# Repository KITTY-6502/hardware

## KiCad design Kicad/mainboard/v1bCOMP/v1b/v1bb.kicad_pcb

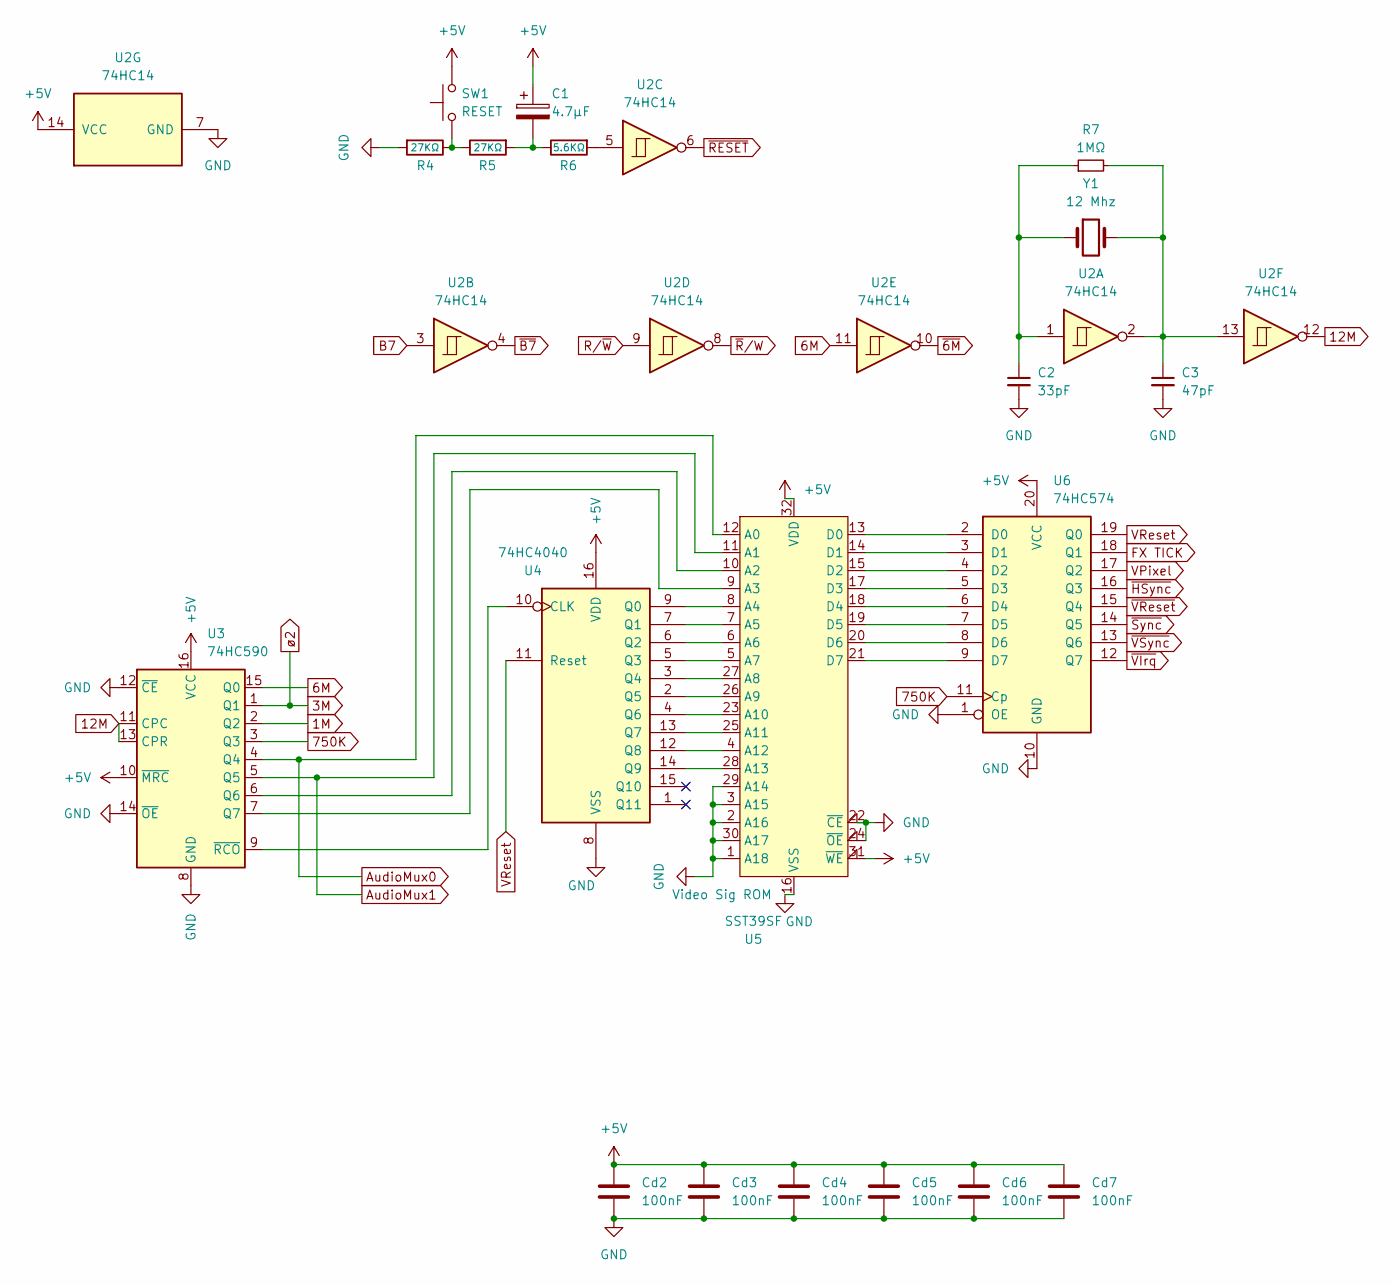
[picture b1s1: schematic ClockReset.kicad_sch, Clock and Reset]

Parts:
C1: 4.7µF; CP_Radial_D4.0mm_P1.50mm
C2: 33pF; C_Disc_D3.0mm_W2.0mm_P2.50mm
C3: 47pF; C_Disc_D3.0mm_W2.0mm_P2.50mm
Cd2, Cd3, Cd4, Cd5, Cd6, Cd7: 100nF; C_Disc_D3.0mm_W2.0mm_P2.50mm
R4, R5: 27KΩ; R_Axial_DIN0204_L3.6mm_D1.6mm_P7.62mm_Horizontal
R6: 5.6KΩ; R_Axial_DIN0204_L3.6mm_D1.6mm_P7.62mm_Horizontal
R7: 1MΩ; R_Axial_DIN0204_L3.6mm_D1.6mm_P7.62mm_Horizontal
SW1: RESET; SW_Tactile_SPST_Angled_PTS645Vx83-2LFS
U2: 74HC14; DIP-14_W7.62mm_Socket_LongPads
U3: 74HC590; DIP-16_W7.62mm_Socket_LongPads
U4: 74HC4040; DIP-16_W7.62mm_Socket_LongPads
U5: SST39SF; PLCC-32_THT-Socket
U6: 74HC574; DIP-20_W7.62mm_Socket_LongPads
Y1: 12 Mhz; Crystal_HC49-U_Vertical

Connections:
1M: U3.2 (Q2); also elsewhere on the board
3M: U3.1 (Q1); also elsewhere on the board
6M: U2.11, U3.15 (Q0); also elsewhere on the board
12M: U2.12, U3.11 (CPC), U3.13 (CPR)
750K: U3.3 (Q3), U6.11 (Cp); also elsewhere on the board
+5V: C1.1, Cd2.1, Cd3.1, Cd4.1, Cd5.1, Cd6.1, Cd7.1, SW1.2, U2.14 (VCC), U3.10 (~MRC), U3.16 (VCC), U4.16 (VDD), U5.31 (~WE), U5.32 (VDD), U6.20 (VCC); also elsewhere on the board
AudioMux0: U3.4 (Q4), U5.12 (A0); also elsewhere on the board
AudioMux1: U3.5 (Q5), U5.11 (A1); also elsewhere on the board
B7: U2.3; also elsewhere on the board
FX TICK: U6.18 (Q1); also elsewhere on the board
GND: C2.2, C3.2, Cd2.2, Cd3.2, Cd4.2, Cd5.2, Cd6.2, Cd7.2, R4.2, U2.7 (GND), U3.8 (GND), U3.12 (~CE), U3.14 (~OE), U4.8 (VSS), U5.1 (A18), U5.2 (A16), U5.3 (A15), U5.16 (VSS), U5.22 (~CE), U5.24 (~OE), U5.29 (A14), U5.30 (A17), U6.1 (OE), U6.10 (GND); also elsewhere on the board
unnamed: C1.2, R5.2, R6.1
unnamed: C2.1, R7.1, U2.1, Y1.1
unnamed: C3.1, R7.2, U2.2, U2.13, Y1.2
unnamed: R4.1, R5.1, SW1.1
unnamed: R6.2, U2.5
unnamed: U3.6 (Q6), U5.10 (A2)
unnamed: U3.7 (Q7), U5.9 (A3)
unnamed: U3.9 (~RCO), U4.10 (CLK)
unnamed: U4.9 (Q0), U5.8 (A4)
unnamed: U4.7 (Q1), U5.7 (A5)
unnamed: U4.6 (Q2), U5.6 (A6)
unnamed: U4.5 (Q3), U5.5 (A7)
unnamed: U4.3 (Q4), U5.27 (A8)
unnamed: U4.2 (Q5), U5.26 (A9)
unnamed: U4.4 (Q6), U5.23 (A10)
unnamed: U4.13 (Q7), U5.25 (A11)
unnamed: U4.12 (Q8), U5.4 (A12)
unnamed: U4.14 (Q9), U5.28 (A13)
unnamed: U5.13 (D0), U6.2 (D0)
unnamed: U5.14 (D1), U6.3 (D1)
unnamed: U5.15 (D2), U6.4 (D2)
unnamed: U5.17 (D3), U6.5 (D3)
unnamed: U5.18 (D4), U6.6 (D4)
unnamed: U5.19 (D5), U6.7 (D5)
unnamed: U5.20 (D6), U6.8 (D6)
unnamed: U5.21 (D7), U6.9 (D7)
R/~W: U2.9; also elsewhere on the board
VPixel: U6.17 (Q2); also elsewhere on the board
VReset: U4.11 (Reset), U6.19 (Q0)
~6M: U2.10; also elsewhere on the board
~B7: U2.4; also elsewhere on the board
~HSync: U6.16 (Q3); also elsewhere on the board
~RESET: U2.6; also elsewhere on the board
~R/W: U2.8; also elsewhere on the board
~Sync: U6.14 (Q5); also elsewhere on the board
~VIrq: U6.12 (Q7); also elsewhere on the board
~VReset: U6.15 (Q4); also elsewhere on the board
~VSync: U6.13 (Q6); also elsewhere on the board

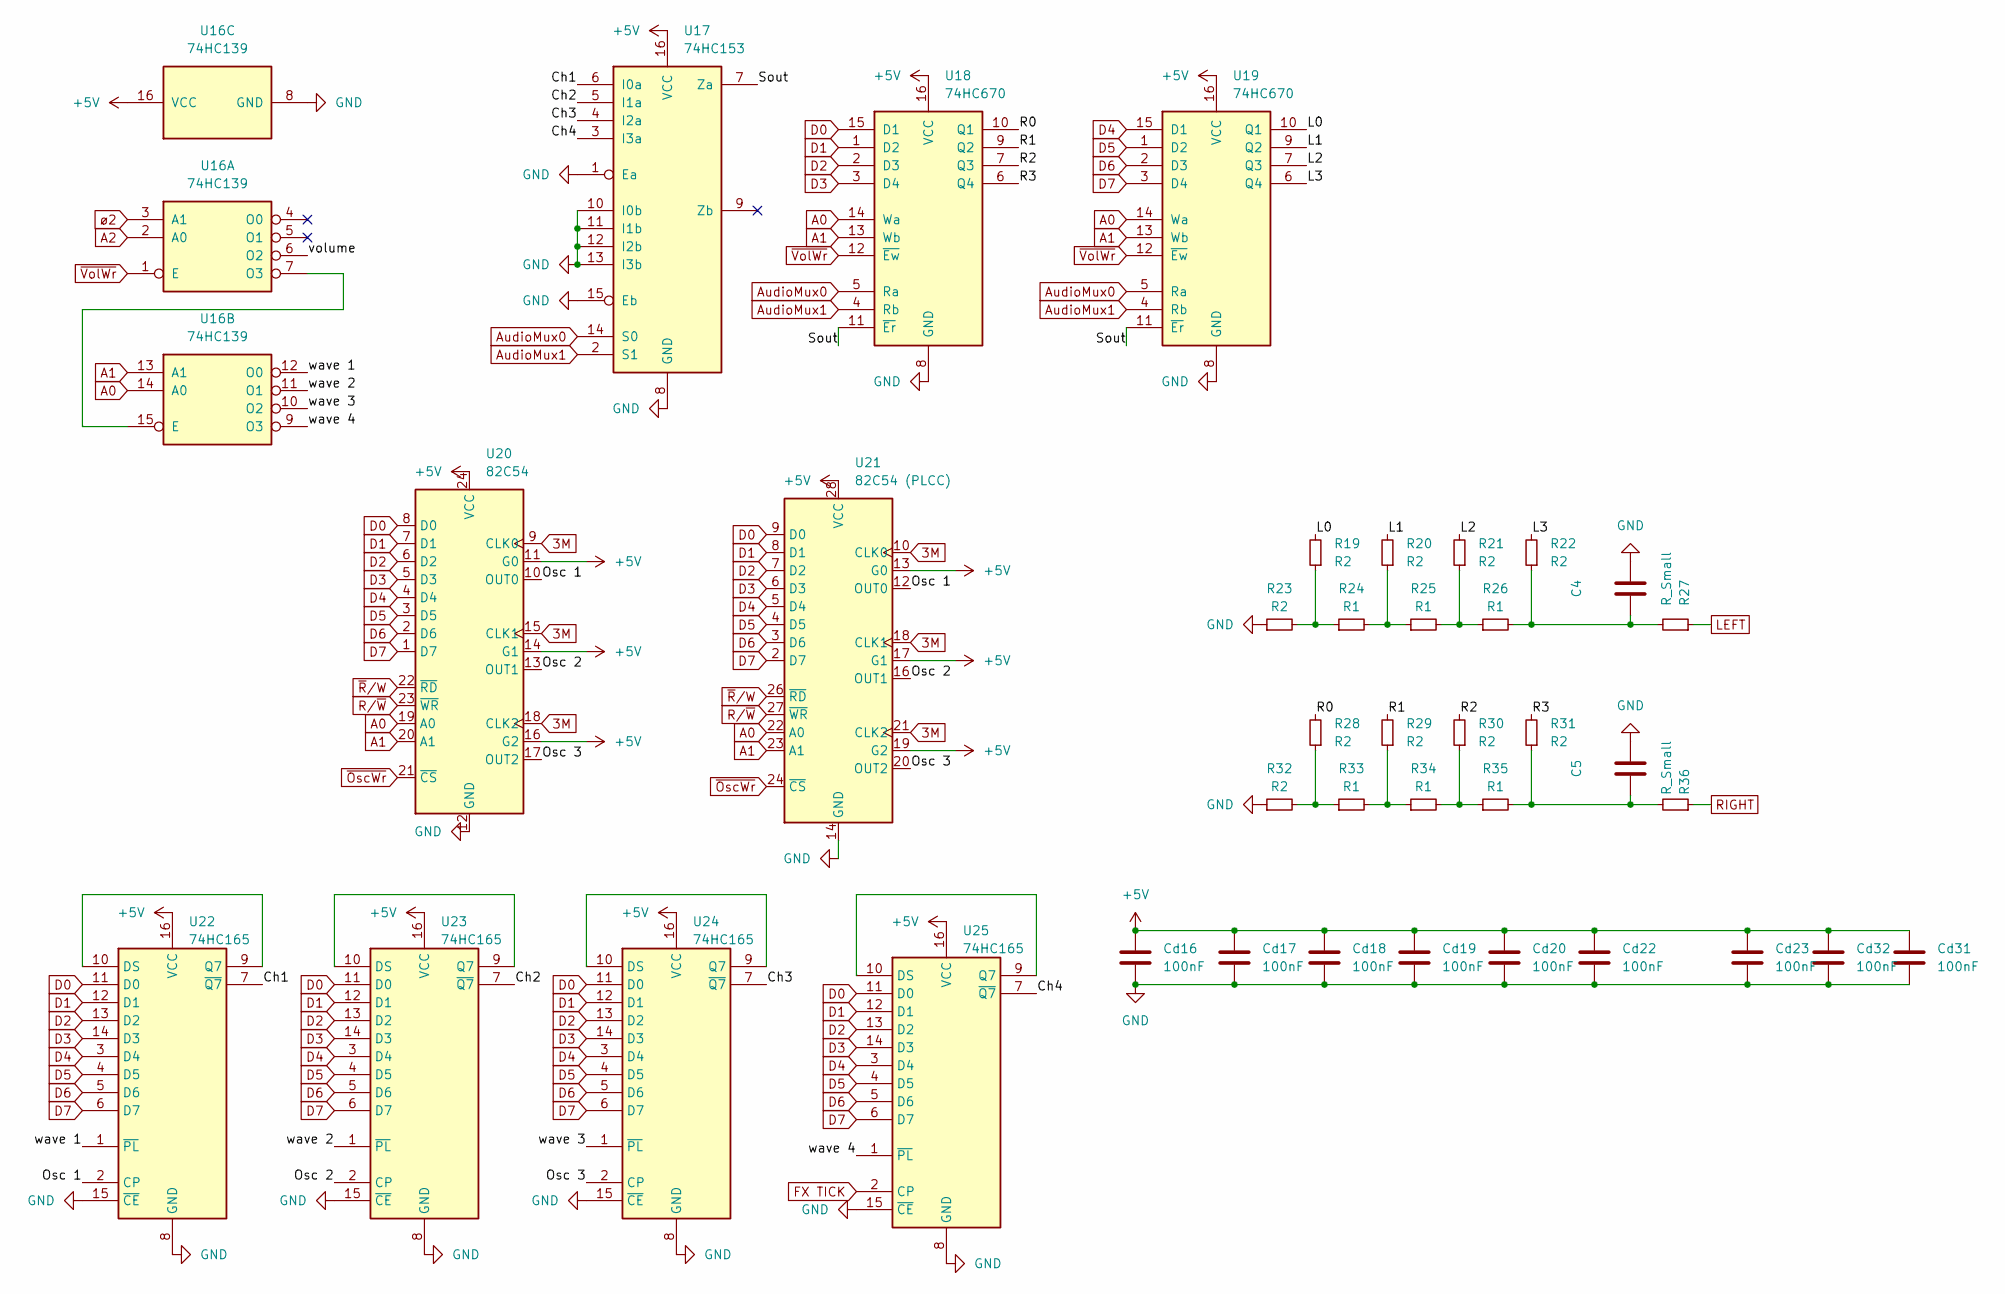
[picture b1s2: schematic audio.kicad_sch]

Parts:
C4, C5: 100nF; C_Disc_D3.0mm_W2.0mm_P2.50mm
Cd16, Cd17, Cd18, Cd19, Cd20, Cd22, Cd23, Cd31, Cd32: 100nF; C_Disc_D3.0mm_W2.0mm_P2.50mm
R19, R20, R21, R22, R23, R28, R29, R30, R31, R32: R2; R_Axial_DIN0204_L3.6mm_D1.6mm_P1.90mm_Vertical
R24, R25, R26, R33, R34, R35: R1; R_Axial_DIN0204_L3.6mm_D1.6mm_P1.90mm_Vertical
R27, R36: R_Small; R_Axial_DIN0204_L3.6mm_D1.6mm_P1.90mm_Vertical
U16: 74HC139; DIP-16_W7.62mm_Socket_LongPads
U17: 74HC153; DIP-16_W7.62mm_Socket_LongPads
U18, U19: 74HC670; DIP-16_W7.62mm_Socket_LongPads
U20: 82C54; DIP-24_W15.24mm_Socket
U21: 82C54 (PLCC); PLCC-28_THT-Socket
U22, U23, U24, U25: 74HC165; DIP-16_W7.62mm_Socket_LongPads

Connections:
3M: U16.3 (A1), U20.9 (CLK0), U20.15 (CLK1), U20.18 (CLK2), U21.10 (CLK0), U21.18 (CLK1), U21.21 (CLK2); also elsewhere on the board
+5V: Cd16.1, Cd17.1, Cd18.1, Cd19.1, Cd20.1, Cd22.1, Cd23.1, Cd31.1, Cd32.1, U16.16 (VCC), U17.16 (VCC), U18.16 (VCC), U19.16 (VCC), U20.11 (G0), U20.14 (G1), U20.16 (G2), U20.24 (VCC), U21.13 (G0), U21.17 (G1), U21.19 (G2), U21.28 (VCC), U22.16 (VCC), U23.16 (VCC), U24.16 (VCC), U25.16 (VCC); also elsewhere on the board
/Audio/Ch1: U17.6 (I0a), U22.7 (~Q7)
/Audio/Ch2: U17.5 (I1a), U23.7 (~Q7)
/Audio/Ch3: U17.4 (I2a), U24.7 (~Q7)
/Audio/Ch4: U17.3 (I3a), U25.7 (~Q7)
/Audio/L0: R19.2, U19.10 (Q1)
/Audio/L1: R20.2, U19.9 (Q2)
/Audio/L2: R21.2, U19.7 (Q3)
/Audio/L3: R22.2, U19.6 (Q4)
/Audio/Osc 1: U20.10 (OUT0), U21.12 (OUT0), U22.2 (CP)
/Audio/Osc 2: U20.13 (OUT1), U21.16 (OUT1), U23.2 (CP)
/Audio/Osc 3: U20.17 (OUT2), U21.20 (OUT2), U24.2 (CP)
/Audio/R0: R28.2, U18.10 (Q1)
/Audio/R1: R29.2, U18.9 (Q2)
/Audio/R2: R30.2, U18.7 (Q3)
/Audio/R3: R31.2, U18.6 (Q4)
/Audio/Sout: U17.7 (Za), U18.11 (~Er), U19.11 (~Er)
/Audio/volume: U16.6 (O2)
/Audio/wave 1: U16.12 (O0), U22.1 (~PL)
/Audio/wave 2: U16.11 (O1), U23.1 (~PL)
/Audio/wave 3: U16.10 (O2), U24.1 (~PL)
/Audio/wave 4: U16.9 (O3), U25.1 (~PL)
A0: U16.14 (A0), U18.14 (Wa), U19.14 (Wa), U20.19 (A0), U21.22 (A0); also elsewhere on the board
A1: U16.13 (A1), U18.13 (Wb), U19.13 (Wb), U20.20 (A1), U21.23 (A1); also elsewhere on the board
A2: U16.2 (A0); also elsewhere on the board
AudioMux0: U17.14 (S0), U18.5 (Ra), U19.5 (Ra); also elsewhere on the board
AudioMux1: U17.2 (S1), U18.4 (Rb), U19.4 (Rb); also elsewhere on the board
D0: U18.15 (D1), U20.8 (D0), U21.9 (D0), U22.11 (D0), U23.11 (D0), U24.11 (D0), U25.11 (D0); also elsewhere on the board
D1: U18.1 (D2), U20.7 (D1), U21.8 (D1), U22.12 (D1), U23.12 (D1), U24.12 (D1), U25.12 (D1); also elsewhere on the board
D2: U18.2 (D3), U20.6 (D2), U21.7 (D2), U22.13 (D2), U23.13 (D2), U24.13 (D2), U25.13 (D2); also elsewhere on the board
D3: U18.3 (D4), U20.5 (D3), U21.6 (D3), U22.14 (D3), U23.14 (D3), U24.14 (D3), U25.14 (D3); also elsewhere on the board
D4: U19.15 (D1), U20.4 (D4), U21.5 (D4), U22.3 (D4), U23.3 (D4), U24.3 (D4), U25.3 (D4); also elsewhere on the board
D5: U19.1 (D2), U20.3 (D5), U21.4 (D5), U22.4 (D5), U23.4 (D5), U24.4 (D5), U25.4 (D5); also elsewhere on the board
D6: U19.2 (D3), U20.2 (D6), U21.3 (D6), U22.5 (D6), U23.5 (D6), U24.5 (D6), U25.5 (D6); also elsewhere on the board
D7: U19.3 (D4), U20.1 (D7), U21.2 (D7), U22.6 (D7), U23.6 (D7), U24.6 (D7), U25.6 (D7); also elsewhere on the board
FX TICK: U25.2 (CP); also elsewhere on the board
GND: C4.1, C5.1, Cd16.2, Cd17.2, Cd18.2, Cd19.2, Cd20.2, Cd22.2, Cd23.2, Cd31.2, Cd32.2, R23.1, R32.1, U16.8 (GND), U17.1 (Ea), U17.8 (GND), U17.10 (I0b), U17.11 (I1b), U17.12 (I2b), U17.13 (I3b), U17.15 (Eb), U18.8 (GND), U19.8 (GND), U20.12 (GND), U21.14 (GND), U22.8 (GND), U22.15 (~CE), U23.8 (GND), U23.15 (~CE), U24.8 (GND), U24.15 (~CE), U25.8 (GND), U25.15 (~CE); also elsewhere on the board
LEFT: R27.1; also elsewhere on the board
unnamed: C4.2, R22.1, R26.2, R27.2
unnamed: C5.2, R31.1, R35.2, R36.2
unnamed: R19.1, R23.2, R24.1
unnamed: R20.1, R24.2, R25.1
unnamed: R21.1, R25.2, R26.1
unnamed: R28.1, R32.2, R33.1
unnamed: R29.1, R33.2, R34.1
unnamed: R30.1, R34.2, R35.1
unnamed: U16.7 (O3), U16.15 (E)
unnamed: U22.9 (Q7), U22.10 (DS)
unnamed: U23.9 (Q7), U23.10 (DS)
unnamed: U24.9 (Q7), U24.10 (DS)
unnamed: U25.9 (Q7), U25.10 (DS)
RIGHT: R36.1; also elsewhere on the board
R/~W: U20.23 (~WR), U21.27 (~WR); also elsewhere on the board
~OscWr: U20.21 (~CS), U21.24 (~CS); also elsewhere on the board
~R/W: U20.22 (~RD), U21.26 (~RD); also elsewhere on the board
~VolWr: U16.1 (E), U18.12 (~Ew), U19.12 (~Ew); also elsewhere on the board

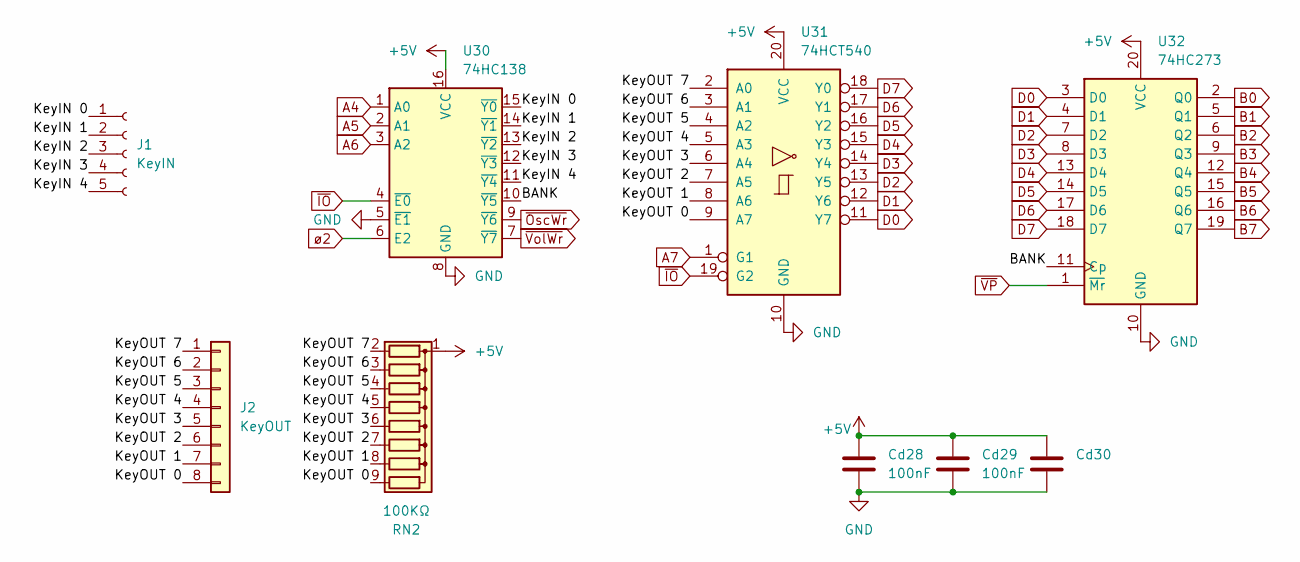
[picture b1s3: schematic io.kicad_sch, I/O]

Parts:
Cd28, Cd29, Cd30: 100nF; C_Disc_D3.0mm_W2.0mm_P2.50mm
J1: KeyIN; PinSocket_1x05_P2.54mm_Vertical
J2: KeyOUT; PinHeader_1x08_P2.54mm_Vertical
RN2: 100KΩ; R_Array_SIP9
U30: 74HC138; DIP-16_W7.62mm_Socket_LongPads
U31: 74HCT540; DIP-20_W7.62mm_Socket_LongPads
U32: 74HC273; DIP-20_W7.62mm_Socket_LongPads

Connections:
3M: U30.6 (E2); also elsewhere on the board
+5V: Cd28.1, Cd29.1, Cd30.1, RN2.1 (common), U30.16 (VCC), U31.20 (VCC), U32.20 (VCC); also elsewhere on the board
/IO/BANK: U30.10 (~Y5), U32.11 (Cp)
/IO/KeyIN 0: J1.1, U30.15 (~Y0)
/IO/KeyIN 1: J1.2, U30.14 (~Y1)
/IO/KeyIN 2: J1.3, U30.13 (~Y2)
/IO/KeyIN 3: J1.4, U30.12 (~Y3)
/IO/KeyIN 4: J1.5, U30.11 (~Y4)
/IO/KeyOUT 0: J2.8, RN2.9 (R8), U31.9 (A7)
/IO/KeyOUT 1: J2.7, RN2.8 (R7), U31.8 (A6)
/IO/KeyOUT 2: J2.6, RN2.7 (R6), U31.7 (A5)
/IO/KeyOUT 3: J2.5, RN2.6 (R5), U31.6 (A4)
/IO/KeyOUT 4: J2.4, RN2.5 (R4), U31.5 (A3)
/IO/KeyOUT 5: J2.3, RN2.4 (R3), U31.4 (A2)
/IO/KeyOUT 6: J2.2, RN2.3 (R2), U31.3 (A1)
/IO/KeyOUT 7: J2.1, RN2.2 (R1), U31.2 (A0)
A4: U30.1 (A0); also elsewhere on the board
A5: U30.2 (A1); also elsewhere on the board
A6: U30.3 (A2); also elsewhere on the board
A7: U31.1 (G1); also elsewhere on the board
B0: U32.2 (Q0); also elsewhere on the board
B1: U32.5 (Q1); also elsewhere on the board
B2: U32.6 (Q2); also elsewhere on the board
B3: U32.9 (Q3); also elsewhere on the board
B4: U32.12 (Q4); also elsewhere on the board
B5: U32.15 (Q5); also elsewhere on the board
B6: U32.16 (Q6); also elsewhere on the board
B7: U32.19 (Q7); also elsewhere on the board
D0: U31.11 (Y7), U32.3 (D0); also elsewhere on the board
D1: U31.12 (Y6), U32.4 (D1); also elsewhere on the board
D2: U31.13 (Y5), U32.7 (D2); also elsewhere on the board
D3: U31.14 (Y4), U32.8 (D3); also elsewhere on the board
D4: U31.15 (Y3), U32.13 (D4); also elsewhere on the board
D5: U31.16 (Y2), U32.14 (D5); also elsewhere on the board
D6: U31.17 (Y1), U32.17 (D6); also elsewhere on the board
D7: U31.18 (Y0), U32.18 (D7); also elsewhere on the board
GND: Cd28.2, Cd29.2, Cd30.2, U30.5 (~E1), U30.8 (GND), U31.10 (GND), U32.10 (GND); also elsewhere on the board
~IO: U30.4 (~E0), U31.19 (G2); also elsewhere on the board
~OscWr: U30.9 (~Y6); also elsewhere on the board
~VP: U32.1 (~Mr); also elsewhere on the board
~VolWr: U30.7 (~Y7); also elsewhere on the board

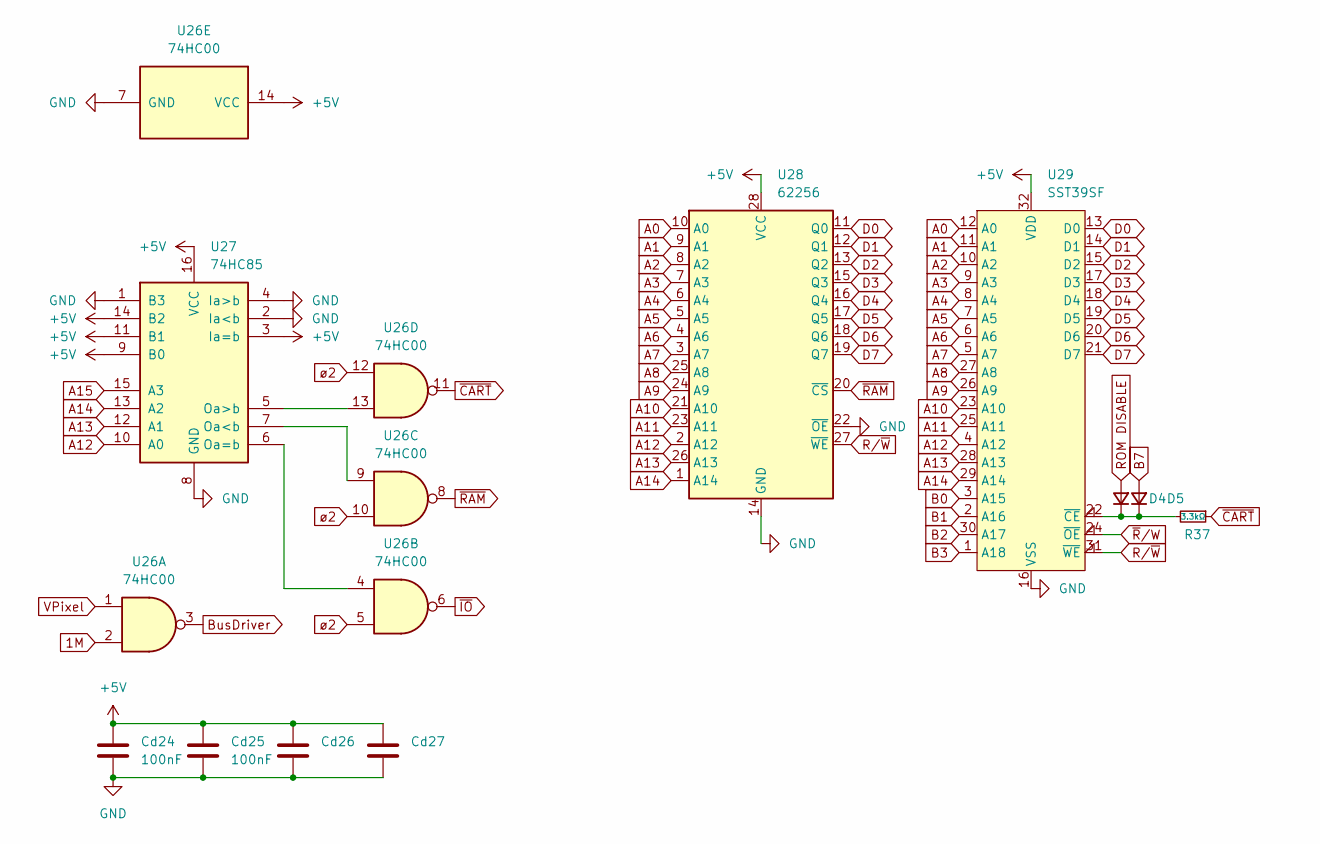
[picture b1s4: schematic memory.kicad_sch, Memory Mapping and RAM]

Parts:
Cd24, Cd25, Cd26, Cd27: 100nF; C_Disc_D3.0mm_W2.0mm_P2.50mm
D4, D5: D_Small; D_DO-34_SOD68_P7.62mm_Horizontal
R37: 3.3kΩ; R_Axial_DIN0204_L3.6mm_D1.6mm_P7.62mm_Horizontal
U26: 74HC00; DIP-14_W7.62mm_Socket_LongPads
U27: 74HC85; DIP-16_W7.62mm_Socket_LongPads
U28: 62256; DIP-28_W15.24mm_Socket_LongPads
U29: SST39SF; PLCC-32_THT-Socket

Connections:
1M: U26.2; also elsewhere on the board
3M: U26.5, U26.10, U26.12; also elsewhere on the board
+5V: Cd24.1, Cd25.1, Cd26.1, Cd27.1, U26.14 (VCC), U27.3 (Ia=b), U27.9 (B0), U27.11 (B1), U27.14 (B2), U27.16 (VCC), U28.28 (VCC), U29.32 (VDD); also elsewhere on the board
A0: U28.10 (A0), U29.12 (A0); also elsewhere on the board
A1: U28.9 (A1), U29.11 (A1); also elsewhere on the board
A2: U28.8 (A2), U29.10 (A2); also elsewhere on the board
A3: U28.7 (A3), U29.9 (A3); also elsewhere on the board
A4: U28.6 (A4), U29.8 (A4); also elsewhere on the board
A5: U28.5 (A5), U29.7 (A5); also elsewhere on the board
A6: U28.4 (A6), U29.6 (A6); also elsewhere on the board
A7: U28.3 (A7), U29.5 (A7); also elsewhere on the board
A8: U28.25 (A8), U29.27 (A8); also elsewhere on the board
A9: U28.24 (A9), U29.26 (A9); also elsewhere on the board
A10: U28.21 (A10), U29.23 (A10); also elsewhere on the board
A11: U28.23 (A11), U29.25 (A11); also elsewhere on the board
A12: U27.10 (A0), U28.2 (A12), U29.4 (A12); also elsewhere on the board
A13: U27.12 (A1), U28.26 (A13), U29.28 (A13); also elsewhere on the board
A14: U27.13 (A2), U28.1 (A14), U29.29 (A14); also elsewhere on the board
A15: U27.15 (A3); also elsewhere on the board
B0: U29.3 (A15); also elsewhere on the board
B1: U29.2 (A16); also elsewhere on the board
B2: U29.30 (A17); also elsewhere on the board
B3: U29.1 (A18); also elsewhere on the board
B7: D5.2 (A); also elsewhere on the board
BusDriver: U26.3; also elsewhere on the board
D0: U28.11 (Q0), U29.13 (D0); also elsewhere on the board
D1: U28.12 (Q1), U29.14 (D1); also elsewhere on the board
D2: U28.13 (Q2), U29.15 (D2); also elsewhere on the board
D3: U28.15 (Q3), U29.17 (D3); also elsewhere on the board
D4: U28.16 (Q4), U29.18 (D4); also elsewhere on the board
D5: U28.17 (Q5), U29.19 (D5); also elsewhere on the board
D6: U28.18 (Q6), U29.20 (D6); also elsewhere on the board
D7: U28.19 (Q7), U29.21 (D7); also elsewhere on the board
GND: Cd24.2, Cd25.2, Cd26.2, Cd27.2, U26.7 (GND), U27.1 (B3), U27.2 (Ia<b), U27.4 (Ia>b), U27.8 (GND), U28.14 (GND), U28.22 (~OE), U29.16 (VSS); also elsewhere on the board
unnamed: D4.1 (K), D5.1 (K), R37.2, U29.22 (~CE)
unnamed: U26.9, U27.7 (Oa<b)
unnamed: U26.4, U27.6 (Oa=b)
unnamed: U26.13, U27.5 (Oa>b)
ROM DISABLE: D4.2 (A); also elsewhere on the board
R/~W: U28.27 (~WE), U29.31 (~WE); also elsewhere on the board
VPixel: U26.1; also elsewhere on the board
~CART: R37.1, U26.11; also elsewhere on the board
~IO: U26.6; also elsewhere on the board
~RAM: U26.8, U28.20 (~CS)
~R/W: U29.24 (~OE); also elsewhere on the board

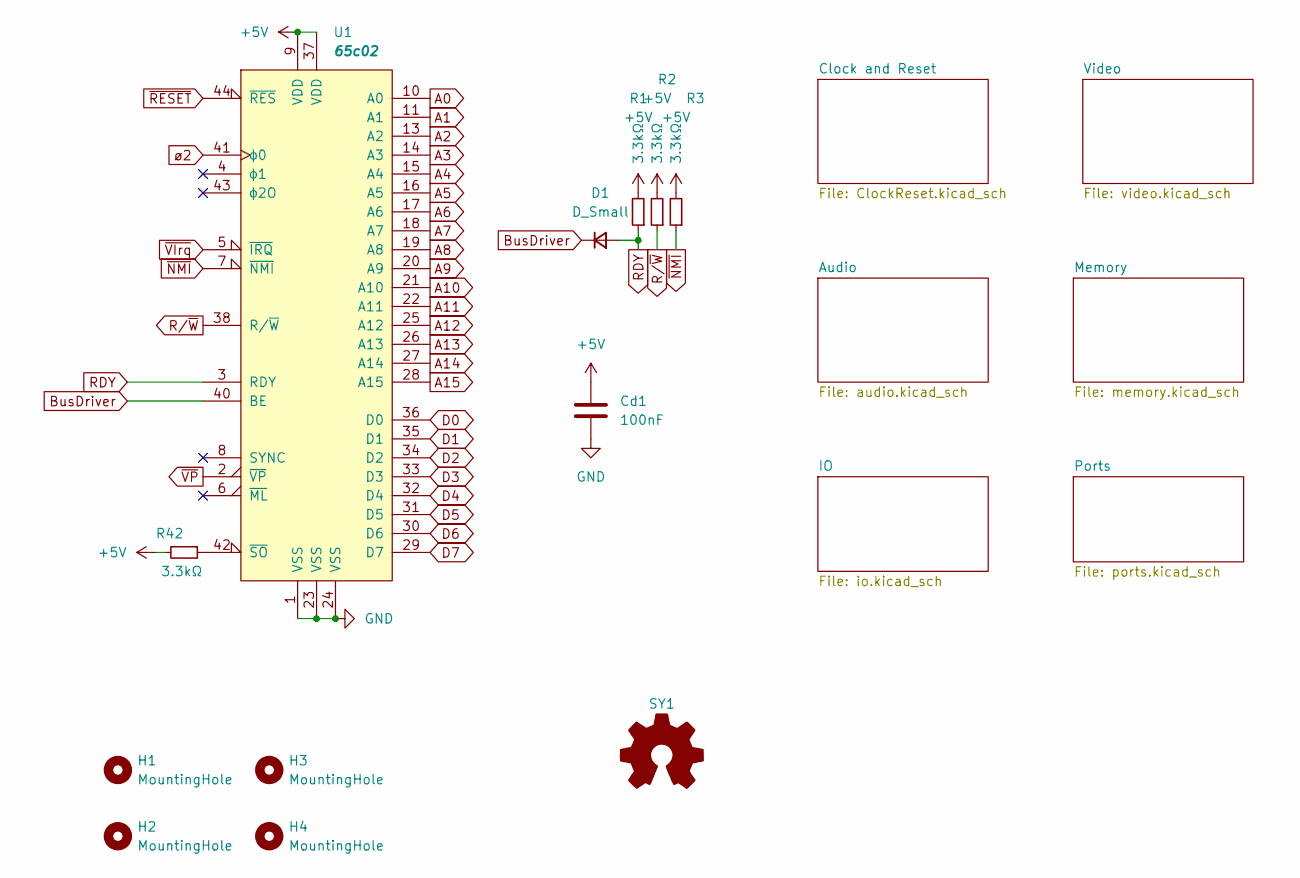
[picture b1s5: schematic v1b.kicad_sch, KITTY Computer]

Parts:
Cd1: 100nF; C_Disc_D3.0mm_W2.0mm_P2.50mm
D1: D_Small; D_DO-34_SOD68_P7.62mm_Horizontal
H1, H2, H3, H4: MountingHole; MountingHole_3.2mm_M3_ISO14580
R1, R2, R3, R42: 3.3kΩ; R_Axial_DIN0204_L3.6mm_D1.6mm_P7.62mm_Horizontal
SY1: Logo_Open_Hardware_Small; OSHW-Logo_7.5x8mm_SilkScreen
U1: 65c02; PLCC-44_THT-Socket

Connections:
3M: U1.41 (ϕ0); also elsewhere on the board
+5V: Cd1.1, R1.2, R2.2, R3.2, R42.2, U1.9 (VDD), U1.37 (VDD); also elsewhere on the board
A0: U1.10 (A0); also elsewhere on the board
A1: U1.11 (A1); also elsewhere on the board
A2: U1.13 (A2); also elsewhere on the board
A3: U1.14 (A3); also elsewhere on the board
A4: U1.15 (A4); also elsewhere on the board
A5: U1.16 (A5); also elsewhere on the board
A6: U1.17 (A6); also elsewhere on the board
A7: U1.18 (A7); also elsewhere on the board
A8: U1.19 (A8); also elsewhere on the board
A9: U1.20 (A9); also elsewhere on the board
A10: U1.21 (A10); also elsewhere on the board
A11: U1.22 (A11); also elsewhere on the board
A12: U1.25 (A12); also elsewhere on the board
A13: U1.26 (A13); also elsewhere on the board
A14: U1.27 (A14); also elsewhere on the board
A15: U1.28 (A15); also elsewhere on the board
BusDriver: D1.1 (K), U1.40 (BE); also elsewhere on the board
D0: U1.36 (D0); also elsewhere on the board
D1: U1.35 (D1); also elsewhere on the board
D2: U1.34 (D2); also elsewhere on the board
D3: U1.33 (D3); also elsewhere on the board
D4: U1.32 (D4); also elsewhere on the board
D5: U1.31 (D5); also elsewhere on the board
D6: U1.30 (D6); also elsewhere on the board
D7: U1.29 (D7); also elsewhere on the board
GND: Cd1.2, U1.1 (VSS), U1.23 (VSS), U1.24 (VSS); also elsewhere on the board
unnamed: R42.1, U1.42 (~SO)
RDY: D1.2 (A), R1.1, U1.3 (RDY)
R/~W: R2.1, U1.38 (R/~W); also elsewhere on the board
~NMI: R3.1, U1.7 (~NMI); also elsewhere on the board
~RESET: U1.44 (~RES); also elsewhere on the board
~VIrq: U1.5 (~IRQ); also elsewhere on the board
~VP: U1.2 (~VP); also elsewhere on the board

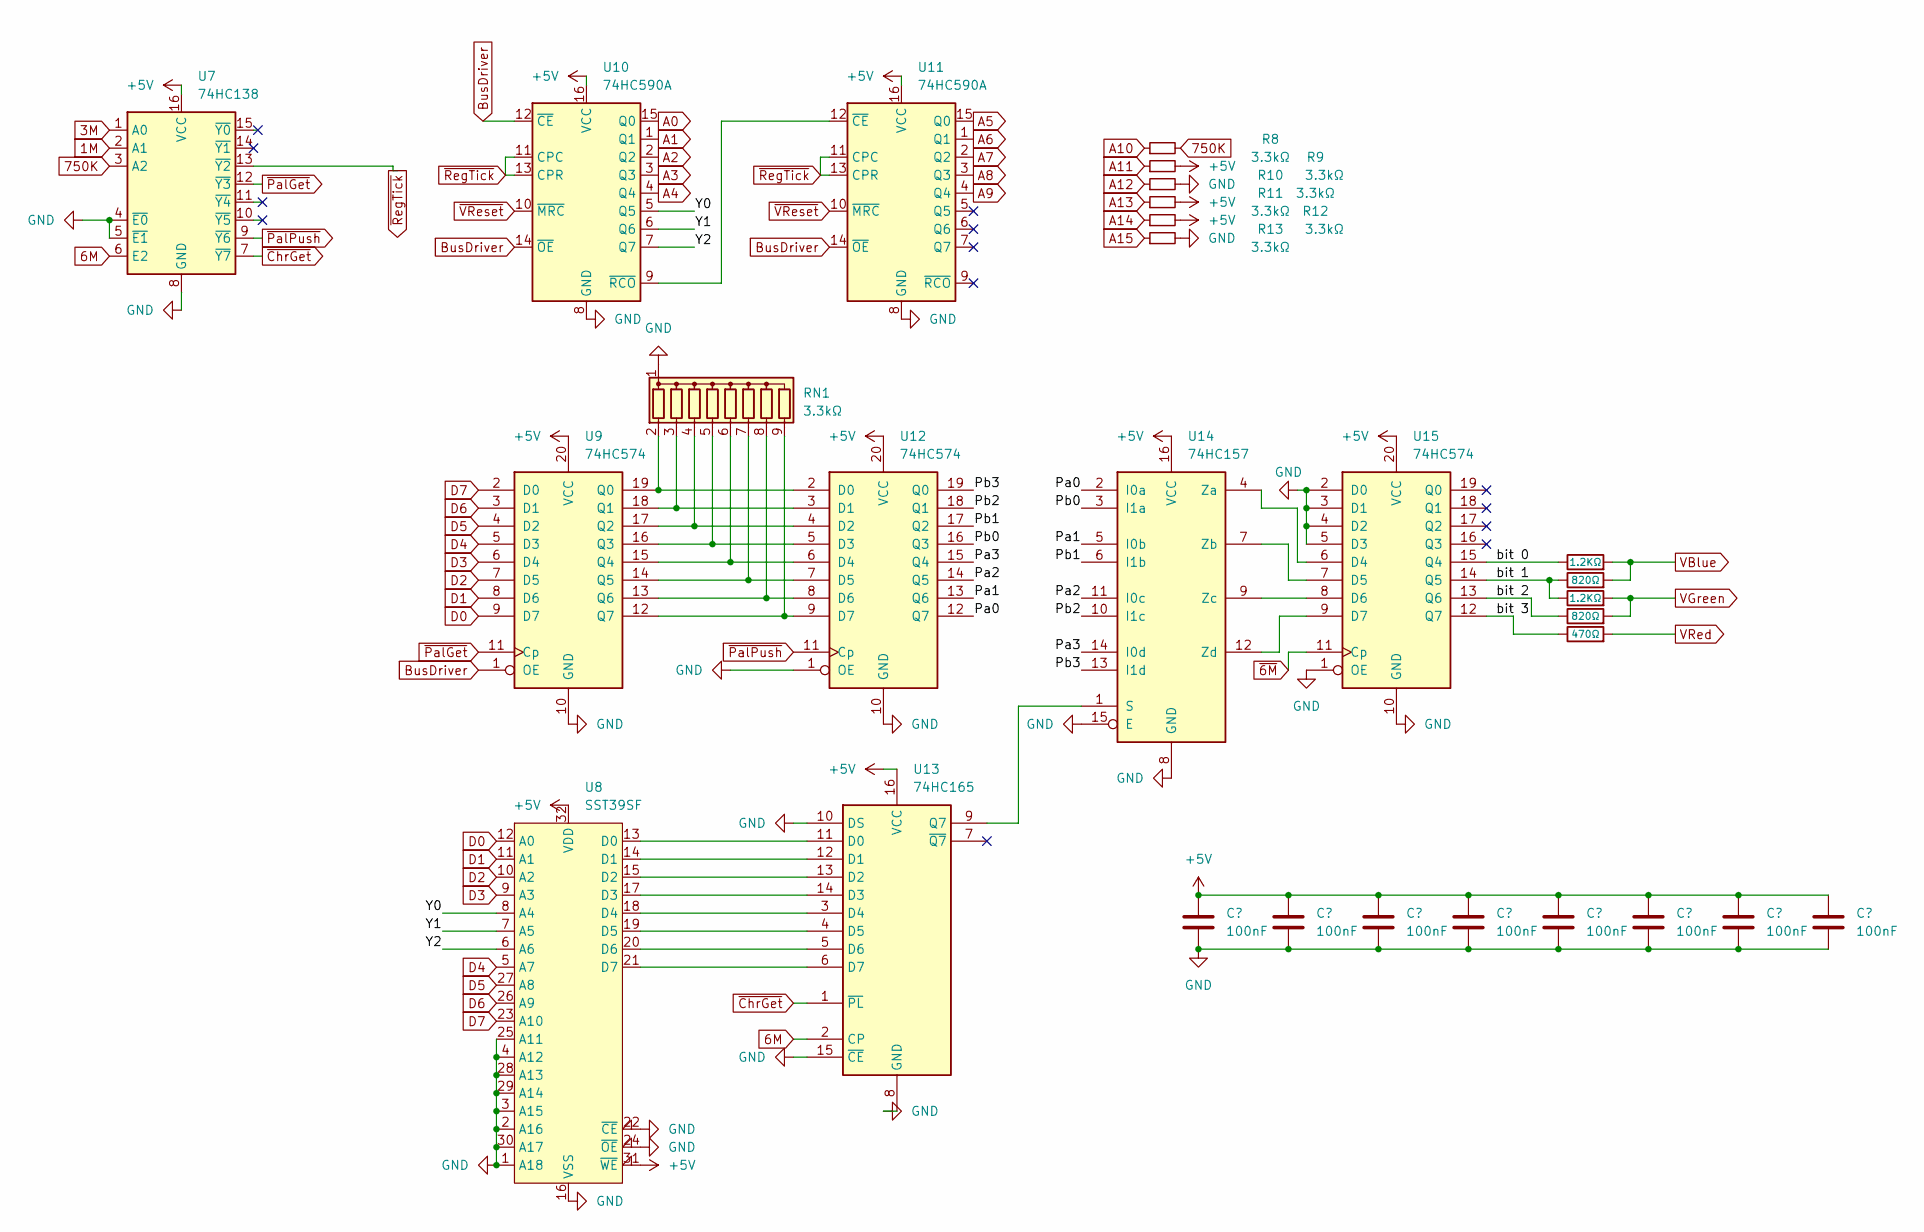
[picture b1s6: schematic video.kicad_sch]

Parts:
Cd8, Cd9, Cd10, Cd11, Cd12, Cd13, Cd14, Cd15: 100nF; C_Disc_D3.0mm_W2.0mm_P2.50mm
R8, R9, R10, R11, R12, R13: 3.3kΩ; R_Axial_DIN0204_L3.6mm_D1.6mm_P7.62mm_Horizontal
R14, R16: 1.2KΩ; R_Axial_DIN0204_L3.6mm_D1.6mm_P7.62mm_Horizontal
R15, R17: 820Ω; R_Axial_DIN0204_L3.6mm_D1.6mm_P7.62mm_Horizontal
R18: 470Ω; R_Axial_DIN0204_L3.6mm_D1.6mm_P7.62mm_Horizontal
RN1: 3.3kΩ; R_Array_SIP9
U7: 74HC138; DIP-16_W7.62mm_Socket_LongPads
U8: SST39SF; PLCC-32_THT-Socket
U9, U12, U15: 74HC574; DIP-20_W7.62mm_Socket_LongPads
U10, U11: 74HC590A; DIP-16_W7.62mm_Socket_LongPads
U13: 74HC165; DIP-16_W7.62mm_Socket_LongPads
U14: 74HC157; DIP-16_W7.62mm_Socket_LongPads

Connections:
1M: U7.2 (A1); also elsewhere on the board
3M: U7.1 (A0); also elsewhere on the board
6M: U7.6 (E2), U13.2 (CP); also elsewhere on the board
750K: R8.2, U7.3 (A2); also elsewhere on the board
+5V: Cd8.1, Cd9.1, Cd10.1, Cd11.1, Cd12.1, Cd13.1, Cd14.1, Cd15.1, R9.2, R11.2, R12.2, U7.16 (VCC), U8.31 (~WE), U8.32 (VDD), U9.20 (VCC), U10.16 (VCC), U11.16 (VCC), U12.20 (VCC), U13.16 (VCC), U14.16 (VCC), U15.20 (VCC); also elsewhere on the board
/Video/Pa0: U12.12 (Q7), U14.2 (I0a)
/Video/Pa1: U12.13 (Q6), U14.5 (I0b)
/Video/Pa2: U12.14 (Q5), U14.11 (I0c)
/Video/Pa3: U12.15 (Q4), U14.14 (I0d)
/Video/Pb0: U12.16 (Q3), U14.3 (I1a)
/Video/Pb1: U12.17 (Q2), U14.6 (I1b)
/Video/Pb2: U12.18 (Q1), U14.10 (I1c)
/Video/Pb3: U12.19 (Q0), U14.13 (I1d)
/Video/Y0: U8.8 (A4), U10.5 (Q5)
/Video/Y1: U8.7 (A5), U10.6 (Q6)
/Video/Y2: U8.6 (A6), U10.7 (Q7)
/Video/bit 0: R14.1, U15.15 (Q4)
/Video/bit 1: R15.1, R16.1, U15.14 (Q5)
/Video/bit 2: R17.1, U15.13 (Q6)
/Video/bit 3: R18.1, U15.12 (Q7)
A0: U10.15 (Q0); also elsewhere on the board
A1: U10.1 (Q1); also elsewhere on the board
A2: U10.2 (Q2); also elsewhere on the board
A3: U10.3 (Q3); also elsewhere on the board
A4: U10.4 (Q4); also elsewhere on the board
A5: U11.15 (Q0); also elsewhere on the board
A6: U11.1 (Q1); also elsewhere on the board
A7: U11.2 (Q2); also elsewhere on the board
A8: U11.3 (Q3); also elsewhere on the board
A9: U11.4 (Q4); also elsewhere on the board
A10: R8.1; also elsewhere on the board
A11: R9.1; also elsewhere on the board
A12: R10.1; also elsewhere on the board
A13: R11.1; also elsewhere on the board
A14: R12.1; also elsewhere on the board
A15: R13.1; also elsewhere on the board
BusDriver: U9.1 (OE), U10.12 (~CE), U10.14 (~OE), U11.14 (~OE); also elsewhere on the board
D0: U8.12 (A0), U9.9 (D7); also elsewhere on the board
D1: U8.11 (A1), U9.8 (D6); also elsewhere on the board
D2: U8.10 (A2), U9.7 (D5); also elsewhere on the board
D3: U8.9 (A3), U9.6 (D4); also elsewhere on the board
D4: U8.5 (A7), U9.5 (D3); also elsewhere on the board
D5: U8.27 (A8), U9.4 (D2); also elsewhere on the board
D6: U8.26 (A9), U9.3 (D1); also elsewhere on the board
D7: U8.23 (A10), U9.2 (D0); also elsewhere on the board
GND: Cd8.2, Cd9.2, Cd10.2, Cd11.2, Cd12.2, Cd13.2, Cd14.2, Cd15.2, R10.2, R13.2, RN1.1 (common), U7.4 (~E0), U7.5 (~E1), U7.8 (GND), U8.1 (A18), U8.2 (A16), U8.3 (A15), U8.4 (A12), U8.16 (VSS), U8.22 (~CE), U8.24 (~OE), U8.25 (A11), U8.28 (A13), U8.29 (A14), U8.30 (A17), U9.10 (GND), U10.8 (GND), U11.8 (GND), U12.1 (OE), U12.10 (GND), U13.8 (GND), U13.10 (DS), U13.15 (~CE), U14.8 (GND), U14.15 (E), U15.1 (OE), U15.2 (D0), U15.3 (D1), U15.4 (D2), U15.5 (D3), U15.10 (GND); also elsewhere on the board
unnamed: RN1.2 (R1), U9.19 (Q0), U12.2 (D0)
unnamed: RN1.3 (R2), U9.18 (Q1), U12.3 (D1)
unnamed: RN1.4 (R3), U9.17 (Q2), U12.4 (D2)
unnamed: RN1.5 (R4), U9.16 (Q3), U12.5 (D3)
unnamed: RN1.6 (R5), U9.15 (Q4), U12.6 (D4)
unnamed: RN1.7 (R6), U9.14 (Q5), U12.7 (D5)
unnamed: RN1.8 (R7), U9.13 (Q6), U12.8 (D6)
unnamed: RN1.9 (R8), U9.12 (Q7), U12.9 (D7)
unnamed: U10.9 (~RCO), U11.12 (~CE)
unnamed: U8.13 (D0), U13.11 (D0)
unnamed: U8.14 (D1), U13.12 (D1)
unnamed: U8.15 (D2), U13.13 (D2)
unnamed: U8.17 (D3), U13.14 (D3)
unnamed: U8.18 (D4), U13.3 (D4)
unnamed: U8.19 (D5), U13.4 (D5)
unnamed: U8.20 (D6), U13.5 (D6)
unnamed: U8.21 (D7), U13.6 (D7)
unnamed: U13.9 (Q7), U14.1 (S)
unnamed: U14.4 (Za), U15.6 (D4)
unnamed: U14.7 (Zb), U15.7 (D5)
unnamed: U14.9 (Zc), U15.8 (D6)
unnamed: U14.12 (Zd), U15.9 (D7)
VBlue: R14.2, R15.2; also elsewhere on the board
VGreen: R16.2, R17.2; also elsewhere on the board
VRed: R18.2; also elsewhere on the board
~6M: U15.11 (Cp); also elsewhere on the board
~ChrGet: U7.7 (~Y7), U13.1 (~PL)
~PalGet: U7.12 (~Y3), U9.11 (Cp)
~PalPush: U7.9 (~Y6), U12.11 (Cp)
~RegTick: U7.13 (~Y2), U10.11 (CPC), U10.13 (CPR), U11.11 (CPC), U11.13 (CPR)
~VReset: U10.10 (~MRC), U11.10 (~MRC); also elsewhere on the board
